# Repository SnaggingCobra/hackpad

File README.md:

# CobraPad

CobraPad is a compact 8-key macro pad built around the Seeed XIAO RP2040, with a rotary encoder, SSD1306 OLED display, addressable RGB underglow, and a custom 3D-printed case. The board and case are treated as the source of truth, and the firmware is mapped directly to the actual KiCad net names and pad assignments.

## Overview

- MCU: Seeed XIAO RP2040
- Layout: 2 rows x 4 columns, 8-key matrix
- Extras: rotary encoder with push switch, 128x32 OLED, 8 SK6812MINI-E LEDs
- Firmware: CircuitPython
- PCB: 2-layer custom board, 99 mm x 99 mm
- Case: custom top and bottom enclosure designed for a fitted assembly

## Project photos

### Overall project / visible build

### Schematic

### PCB

### Case fit / enclosure

## Hardware summary

| Component | Quantity | Notes |
| --- | ---: | --- |
| Seeed XIAO RP2040 | 1 | Main controller |
| Mechanical switches | 8 | Key matrix |
| Diode (1N4148 or equivalent) | 8 | One per switch |
| Rotary encoder with switch | 1 | EC11-style encoder |
| SSD1306 128x32 OLED | 1 | I2C display |
| SK6812MINI-E RGB LEDs | 8 | Addressable LED chain |
| Decoupling capacitor | 3 | Power filtering |
| Resistor | 1 | Pull-up / support |
| 3D-printed case parts | 1 set | Top and bottom shell |
| M2 hardware | 4+ | Case assembly |

## Verified board pin mapping

The firmware in [Firmware/circuitpython/code.py](Firmware/circuitpython/code.py) is mapped to the board as follows:

| Function | KiCad signal / board net | CircuitPython pin |
| --- | --- | --- |
| Row 1 | PA02_A0_D0 | D0 |
| Row 2 | PA4_A1_D1 | D1 |
| Col 1 | PA10_A2_D2 | D2 |
| Col 2 | PA11_A3_D3 | D3 |
| Col 3 | PB08_A6_D6_TX | D6 |
| Col 4 | PB09_A7_D7_RX | D7 |
| OLED SDA | PA8_A4_D4_SDA | D4 |
| OLED SCL | PA9_A5_D5_SCL | D5 |
| Encoder A | PA7_A8_D8_SCK | D8 |
| Encoder B | PA5_A9_D9_MISO | D9 |
| LED data | PA6_A10_D10_MOSI | D10 |

## BOM

The table below is the verified BOM for the current KiCad schematic and board assembly.

| Component | Quantity | Description |
| --- | ---: | --- |
| Seeed XIAO RP2040 | 1 | Main microcontroller board |
| Mechanical keyboard switch | 8 | Cherry MX-compatible switches for the key matrix |
| 1N4148 diode | 8 | One diode per switch for matrix protection and flyback suppression |
| SK6812MINI-E RGB LED | 8 | Addressable underglow/lighting LEDs |
| SSD1306 128x32 OLED module | 1 | I2C display for status and output |
| Rotary encoder with push switch | 1 | EC11-style encoder for control input |
| 100 nF decoupling capacitor | 8 | SMD power-filter capacitors used across the board (C1-C8) |
| M2 case mounting hardware | 4 | Screws/standoffs used for the enclosure assembly |
| 3D-printed top shell | 1 | Custom top enclosure cover |
| 3D-printed bottom shell | 1 | Custom bottom enclosure base |

See [BOM.csv](BOM.csv) for the CSV version of the same parts list.

## Repository layout

- [PCB/CobraPad](PCB/CobraPad) — KiCad PCB, schematic, and project files
- [kicad-libs](kicad-libs) — custom symbols and library files
- [CAD](CAD) — assembled CAD and mechanical source files
- [CAD/Case](CAD/Case) — case source and generated shell files
- [Firmware](Firmware) — CircuitPython firmware and notes
- [assets](assets) — project screenshots and render images
- [production](production) — manufacturing and production outputs
- [BOM.csv](BOM.csv) — project components list
- [LICENSE](LICENSE) — project license

## Production files

The final project includes fabrication and production artifacts in [production](production):

- [production/gerbers.zip](production/gerbers.zip) — PCB fabrication Gerbers and drill files
- [production/CobraPad.step](production/CobraPad.step) — PCB STEP export
- [production/CobraPAD_CASE_FINAL_top_cover.step](production/CobraPAD_CASE_FINAL_top_cover.step) — case top shell
- [production/CobraPAD_CASE_Finalbottom_shell.step](production/CobraPAD_CASE_Finalbottom_shell.step) — case bottom shell
- [production/CobraPad_circuitpython.zip](production/CobraPad_circuitpython.zip) — firmware bundle

## CAD and enclosure

The assembled CAD model is located in [CAD/CobraPAD_All together.step](CAD/CobraPAD_All%20together.step). This file represents the assembled project geometry and includes the designed enclosure plus the PCB in context. The project also includes the editable FreeCAD source file in [CAD/Final.FCStd](CAD/Final.FCStd).

## Firmware

The active firmware is written in CircuitPython and lives in [Firmware/circuitpython/code.py](Firmware/circuitpython/code.py). The companion notes are in [Firmware/README.md](Firmware/README.md).

### Firmware capabilities

- 8-key matrix scanning
- rotary encoder clockwise / counter-clockwise detection
- encoder push-button input
- SSD1306 display output
- 8-addressable RGB LED support
- USB HID keyboard output

## Build / setup notes

1. Open [PCB/CobraPad/CobraPad.kicad_pro](PCB/CobraPad/CobraPad.kicad_pro) in KiCad.
2. Verify the board matches the schematic and intended parts list.
3. Flash CircuitPython onto the XIAO RP2040.
4. Copy the contents of [Firmware/circuitpython](Firmware/circuitpython) onto the CIRCUITPY drive.
5. Assemble the PCB, case, encoder, OLED, and LEDs.
6. Validate key presses, encoder behavior, display output, and LED animation.

## Design notes

- The KiCad PCB and case files are the source of truth for this project.
- The board is intentionally mapped to the specific RP2040 pins used in the hardware.
- The firmware is designed to match the actual board connection map and component placement.
- The project is meant to be a compact, low-profile macro pad with a clean custom enclosure.

## Project status

This repository is prepared as a final project archive and submission bundle for the CobraPad macro pad. The current project includes the final PCB source, fabricated production outputs, custom case files, and the CircuitPython firmware.

## License

This project is released under the MIT license. See [LICENSE](LICENSE).

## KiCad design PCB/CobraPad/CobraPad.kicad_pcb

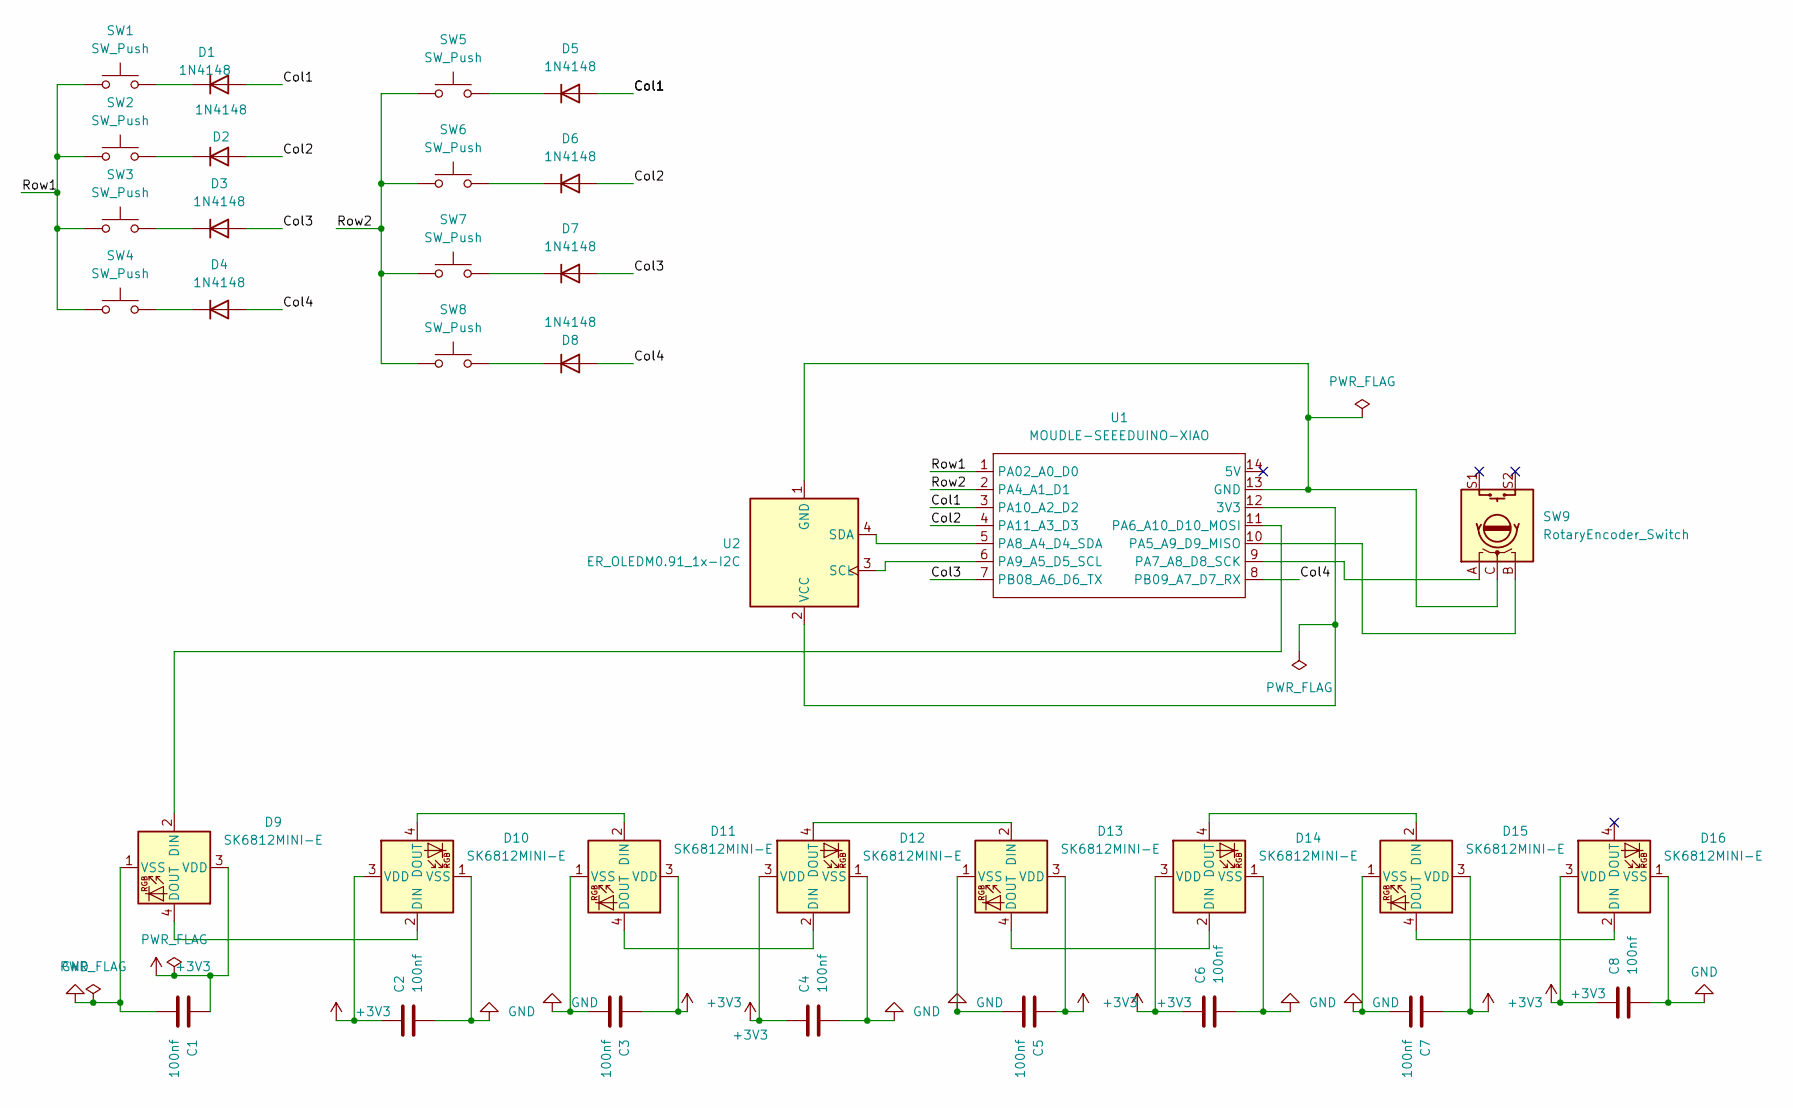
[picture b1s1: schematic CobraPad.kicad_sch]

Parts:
C1, C2, C3, C4, C5, C6, C7, C8: 100nf; C_0603_1608Metric
D1, D2, D3, D4, D5, D6, D7, D8: 1N4148; D_DO-35_SOD27_P7.62mm_Horizontal
D9, D10, D11, D12, D13, D14, D15, D16: SK6812MINI-E; LED_SK6812MINI-E_3.2x2.8mm_P1.5mm_ReverseMount
SW1, SW2, SW3, SW4, SW5, SW6, SW7, SW8: SW_Push; SW_Cherry_MX_1.00u_Plate
SW9: RotaryEncoder_Switch; RotaryEncoder_Alps_EC11E-Switch_Vertical_H20mm
U1: MOUDLE-SEEEDUINO-XIAO; XIAO-Generic-Hybrid-14P-2.54-21X17.8MM
U2: ER_OLEDM0.91_1x-I2C

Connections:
+3V3: C1.1, C2.1, C3.1, C4.1, C5.1, C6.1, C7.1, C8.1, D9.3 (VDD), D10.3 (VDD), D11.3 (VDD), D12.3 (VDD), D13.3 (VDD), D14.3 (VDD), D15.3 (VDD), D16.3 (VDD)
/Col1: D1.2 (A), D5.2 (A), U1.3 (PA10_A2_D2)
/Col2: D2.2 (A), D6.2 (A), U1.4 (PA11_A3_D3)
/Col3: D3.2 (A), D7.2 (A), U1.7 (PB08_A6_D6_TX)
/Col4: D4.2 (A), D8.2 (A), U1.8 (PB09_A7_D7_RX)
/Row1: SW1.1, SW2.1, SW3.1, SW4.1, U1.1 (PA02_A0_D0)
/Row2: SW5.1, SW6.1, SW7.1, SW8.1, U1.2 (PA4_A1_D1)
GND: C1.2, C2.2, C3.2, C4.2, C5.2, C6.2, C7.2, C8.2, D9.1 (VSS), D10.1 (VSS), D11.1 (VSS), D12.1 (VSS), D13.1 (VSS), D14.1 (VSS), D15.1 (VSS), D16.1 (VSS)
unnamed: D1.1 (K), SW1.2
unnamed: D2.1 (K), SW2.2
unnamed: D3.1 (K), SW3.2
unnamed: D4.1 (K), SW4.2
unnamed: D5.1 (K), SW5.2
unnamed: D6.1 (K), SW6.2
unnamed: D7.1 (K), SW7.2
unnamed: D8.1 (K), SW8.2
unnamed: D9.2 (DIN), U1.11 (PA6_A10_D10_MOSI)
unnamed: D9.4 (DOUT), D10.2 (DIN)
unnamed: D10.4 (DOUT), D11.2 (DIN)
unnamed: D11.4 (DOUT), D12.2 (DIN)
unnamed: D12.4 (DOUT), D13.2 (DIN)
unnamed: D13.4 (DOUT), D14.2 (DIN)
unnamed: D14.4 (DOUT), D15.2 (DIN)
unnamed: D15.4 (DOUT), D16.2 (DIN)
unnamed: U1.12 (3V3), U2.2 (VCC)
unnamed: SW9.C, U1.13 (GND), U2.1 (GND)
unnamed: SW9.B, U1.10 (PA5_A9_D9_MISO)
unnamed: SW9.A, U1.9 (PA7_A8_D8_SCK)
unnamed: U1.5 (PA8_A4_D4_SDA), U2.4 (SDA)
unnamed: U1.6 (PA9_A5_D5_SCL), U2.3 (SCL)

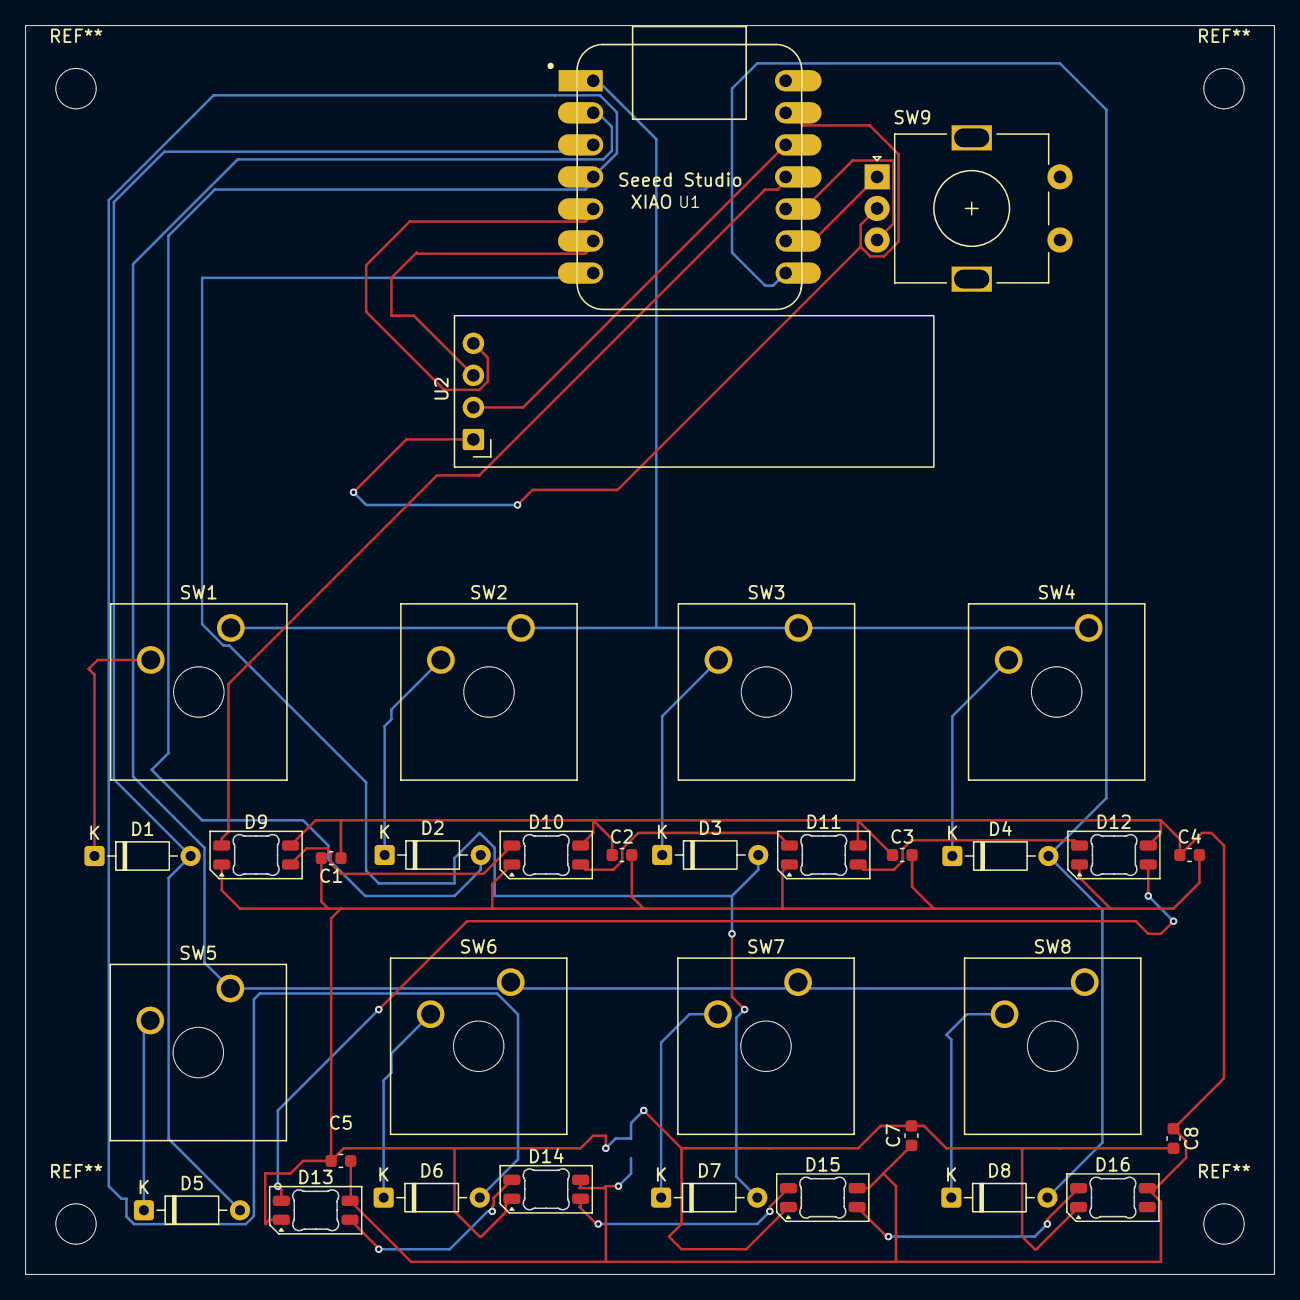
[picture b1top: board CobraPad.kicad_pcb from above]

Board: 2 copper layers, 99.0 x 99.0 mm, 35 parts (1 on the bottom side), 30 nets.
